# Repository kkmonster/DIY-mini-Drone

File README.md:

DIY-mini-Drone
==============

diy project mini drone from chiangmai maker club

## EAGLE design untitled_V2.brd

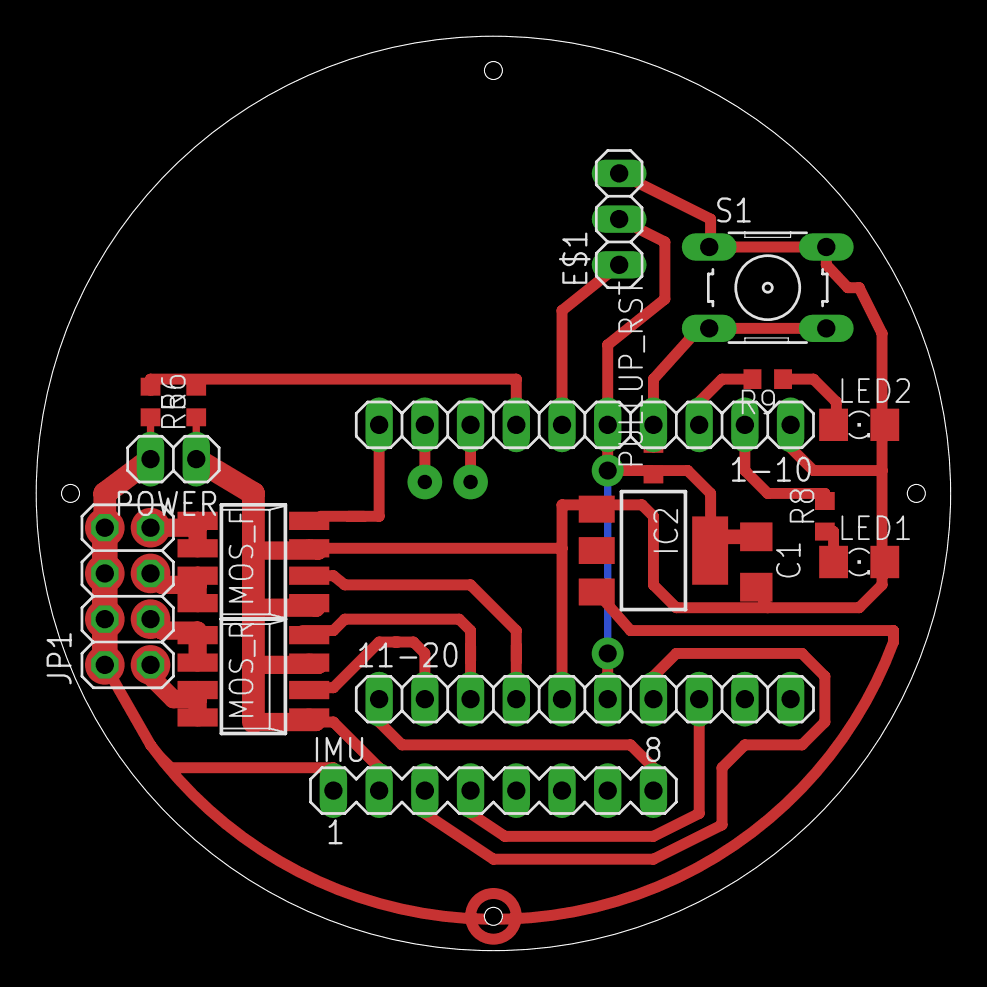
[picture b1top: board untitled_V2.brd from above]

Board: 2 copper layers, 50.8 x 50.8 mm, 18 parts (0 on the bottom side), 16 nets.

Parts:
1-10, 11-20: 1X10
C1: C1206
E$1: 1X03
IC2: LD117AS33TR; SOT223
IMU: MA08-1
JP1: 2X04
LED1, LED2: 1206
MOS_F: SM8
MOS_R: SM8
POWER: 1X02
PULLUP_RST: R0603
R5, R6, R8, R9: R0603
S1: B3F-10XX

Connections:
GND: 1-10.1, 11-20.5, C1.2, IC2.1, IMU.2, LED1.C, LED2.C, MOS_F.1, MOS_F.3, MOS_R.1, MOS_R.3, POWER.1, R6.1, S1.1, S1.2
unnamed: JP1.7, MOS_F.5, MOS_F.6
unnamed: JP1.5, MOS_F.7, MOS_F.8
unnamed: JP1.3, MOS_R.5, MOS_R.6
unnamed: JP1.1, MOS_R.7, MOS_R.8
unnamed: 1-10.5, 11-20.6, C1.1, E$1.2, IC2.4, PULLUP_RST.1
unnamed: 1-10.4, PULLUP_RST.2, S1.3, S1.4
unnamed: 11-20.7, IMU.3
unnamed: 11-20.8, IMU.4
unnamed: LED1.A, R8.1
unnamed: 11-20.1, IMU.8
unnamed: 1-10.2, R8.2
unnamed: 1-10.3, R9.2
unnamed: LED2.A, R9.1
S$5: 1-10.6, E$1.1
VCC: IC2.3, IMU.1, JP1.2, JP1.4, JP1.6, JP1.8, POWER.2, R5.2

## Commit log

2014-10-26 add borad & pcb
2014-10-27 add ignore file
2014-10-27 limit maximum motor value
2014-10-31 add quaternion, gyro diff, start_pitch, start_roll
2014-10-31 cleaning
2014-10-31 cleaning add low voltage protect add easy yaw control set controller loop to 250 hz
2014-11-01 tune all gain add low battery protect add angle compensate add start referent
2014-11-01 fixed bug, disable ch5
2014-11-02 Bluetooth new branch
2014-11-02 mem full
2014-11-02 fixed bug finish
2014-11-05 Change Speed Controller loop to 250 Hz
2014-11-05 recode
2014-11-05 add uart
2014-11-05 PID >> PD // Full memory
2014-11-05 fixed code bug
2014-11-05 Success receive data with uart
    condition
    0xff ch1 ch2 ch3 ch4 0xff ch1 ch2 ch3 ch4
    10byte per a comunication
2014-11-05 add protection
2014-11-06 fail
2014-11-06 ss2 ก่อนเปลี่ยน ตัวแปร
2014-11-06 debug ble
2014-11-07 change const float >>> #define
2014-11-07 fixed
2014-11-07 change priority
2014-11-08 add data
2014-11-09 ble bug
2014-11-15 sssss
2014-11-19 add file
2014-11-22 fixed feed forward
2014-11-22 no message
2015-03-01 fixed sampling to 250 hz
2015-03-01 atan2 >> atan2f
2015-05-11 เปลี่ยน gyro diff เป็นค่าคงที่
